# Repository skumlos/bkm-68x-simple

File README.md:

BKM-68X alternative input board

This project aims to serve as an alternative to the crazy expensive Sony BKM-68X RGB/YPbPr
input card for Sony BVM-A monitors like the BVM-A14F5, A20F1, A24E1W and A32E1W (M/U/A).

The board is rather simple albeit has some components that are not so simple to hand solder,
and it also has a quite high component count (due to a load of resistors and caps).

It's buildup is basically an analog section that deals with video, and a digital section
that speaks to the monitor.

The analog section buffers the video by an THS7374 (with the LPF disabled!) and throws
those through an ADG1611 (or compatible) switch, working via the VIDEO_OE_X signal from
the FPGA. The Y/G signal is first routed through an ISL4089 which strips the sync part 
(if needed) from the signal to avoid too bright picture in YPbPr and SoG signals. This
is however only done if the input is YPbPr at 480p and below and for RGsB signals.
In version 1.1 of the software, this can be switched by turning aperture on. This might
be removed later though, as this is somewhat for testing.

The sync signal is separated through an ISL59885 with a color filter in front (as per
the datasheet), and the signal to be separated (external or Y signal) is chosen via
INT_EXT_X signal to an FSA2257MUX switch.

These are then passed to the FPGA which detects sync polarity and changes accordingly
to positive sync, and then sends the two signals into the monitor.

The digital section consists of a FPGA (efinix Trion T8Q144) with a buttload of schmitt
triggers and line drivers, all replicated from the original 68X service manual. The
card thus tries to be electrically similar to the original, at the interface level.

The FPGA is expected to be programmed with the HDL from https://github.com/skumlos/bkm-68x-fpga

75 Ohm termination can be selected by the switches, which either terminates, or passthroughs
(in that case external terminators are needed, unless signal is actually passed through to a
terminating monitor).

The card has no aperture circuit so it can only pass the signal straight through to the monitor
as it originally is (buffered and level conditioned).

Compared to the original BKM-68X, this has severely better sync handling seemingly.

The list of tested consoles that syncs fine as of revision E1 is:

SNES (2CHIP US) 60Hz (CSYNC)

SNES (1CHIP FAT US) 60Hz (CSYNC)

SNES (2CHIP EU) 50Hz (Sync on luma)

SNES (1CHIP EU, SNSP-1CHIP-01) 50Hz (Sync on luma)

Genesis (US) 60Hz (CVBS sync)

Genesis 2 (US) 60Hz (CSYNC)

Mega Drive (EU) 50Hz (CVBS sync)

Mega Drive 2 (EU, DFO) 60Hz (CSYNC)

Mega Drive 2 (EU, DFO) 50Hz (CSYNC)

Master System (on Genesis through Power Base) 60Hz (CVBS sync)

Master System (EU, DFO) 60Hz (CSYNC)

Master System (EU, DFO) 50Hz (CSYNC)

Master System (EU, VA3, no DFO) 60Hz (59,38Hz) (CSYNC)

Master System (EU, VA3, no DFO) 50Hz (CSYNC)

Nintendo 64 (NUSJ) 60Hz (THS7314 RGB) (CSYNC)

Wii (EU) 576i 50Hz (YPbPr)

Wii (EU) 480i 60Hz (YPbPr)

Wii (EU) 480p 60Hz (YPbPr)

PSone SCPH-101 (EU) (MM3+MFO) 60Hz (RGC CSYNC)

PSone SCPH-101 (EU) (MM3+MFO) 50Hz (RGC CSYNC)

PS2 (US) 240p/480i 60Hz (RGBS)

PS2 (US) 480p 60Hz (RGsB)

PS2 (US) 240p/480i/480p (YPbPr)

PS3 (EU) 576i 50Hz (YPbPr)

PS3 (EU) 576p 50Hz (YPbPr)

PS3 (EU) 720p 60Hz (YPbPr)

PS3 (EU) 1080i 60Hz (YPbPr)

PC Engine (White), External RGB mod (THS7374, Genesis 2 plug), 60Hz (CSYNC)

Analogue Nt Mini 2.0 60Hz RGBS (so CSYNC)

Amiga 500 RGBS (PAL) 50Hz (CSYNC)

Xbox 360 (EU) 480i/480p/720p 50/60Hz (YPbPr)

Xbox 360 (EU) 1080i 60Hz (YPbPr) (1080i 50Hz seems to just flicker. Does the same with original 68X)

A load of MiSTer cores which are normally deemed problematic, including DoDonPachi
whose whack VSYNC of 57.6 Hz makes the original BKM-68X scroll the picture with a
steady OSD, while this version has a steady picture with a rolling OSD :)

Master System with CVBS sync works, but sometimes "glitches". This is apparently
due to the quite noisy CVBS signal, which the sync separator picks up. Without
the color filter it is unusable.

It is generally recommended to use CSYNC signals at 75 Ohm levels.

Revision history:

F1-5: A ton of changes, most notably Intel MAX10 FPGA has been change to efinix Trion T8Q144 and ADG734 -> FSA2257MUX

E1: Add "proper" 5V->3.3V translation for sync lines

E: Add "Y/G normalization" control from FPGA

D1: Add STBY_5V pinheader for easier outside-monitor-programming of FPGA.

D: Add DC restore and sync-removal circuit on Y/G line

C1: Minor layout changes

C: Added mounting screw brackets and shortened board for a PCB front, change switch to LFCSP version

B: Added onboard FPGA, color filter, rerouted signals.

A: Initial version

More information @ https://www.immerhax.com

Credits:
Mathias Hyldgaard for providing me with a BVM-A20, which initiated the whole project!
Bob from RetroRGB for testing and listening to my woes :)
The secret benefactor(s) of the original BKM-68X which made the whole project much easier, and ultimately made it possible!
Steve Nutter for being a helpful guy within the pro monitor scene!
The people on the CRT discord and Professional and Broadcast Monitor Facebook group!

(2021) Martin Hejnfelt, martin@hejnfelt.com

This work is released under the CERN Open Hardware Licence version 2 (CERN-OHL-W), see LICENCE.TXT

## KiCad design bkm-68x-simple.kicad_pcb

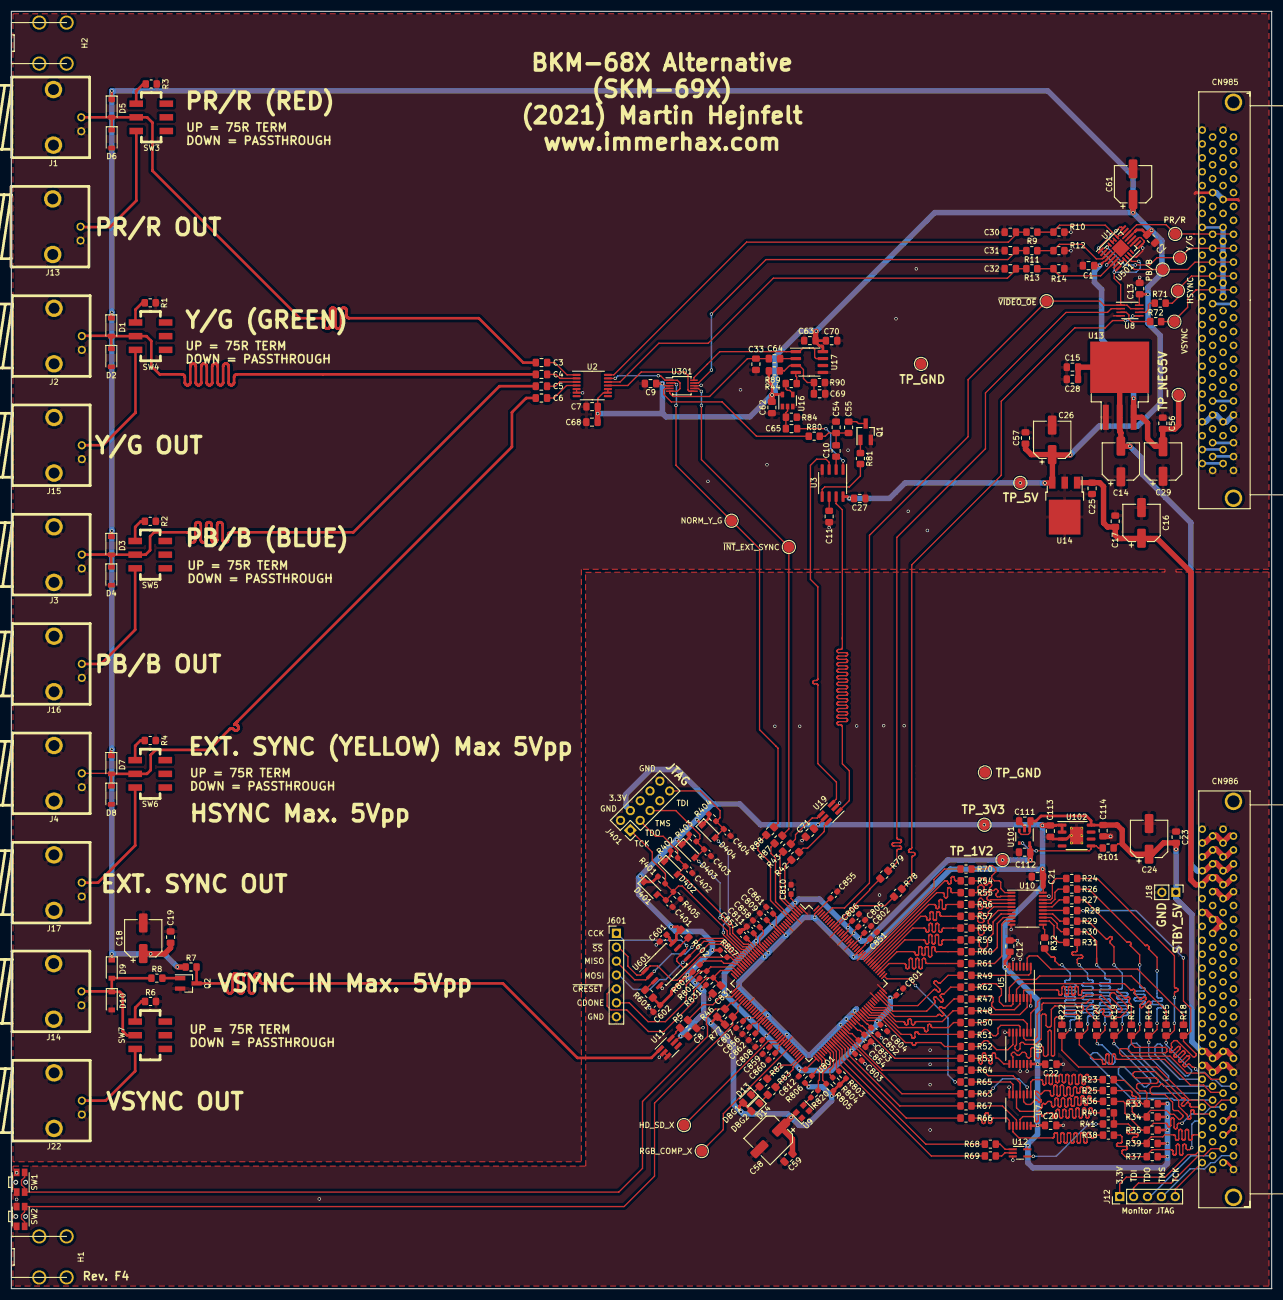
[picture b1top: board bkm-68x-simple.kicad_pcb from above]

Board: 2 copper layers, 230.4 x 233.5 mm, 264 parts (0 on the bottom side), 197 nets.

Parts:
C1, C2, C3, C4, C5, C6, C7, C8, C9, C10, C12, C13, C15, C17, C19, C20, C21, C22, C27, C56, C57, C59, C62, C63, C64, C71: 0.1uF; C_0805_2012Metric_Pad1.18x1.45mm_HandSolder
C11: 56nF; C_0805_2012Metric_Pad1.18x1.45mm_HandSolder
C14, C16, C18, C61: 100uF; CP_Elec_6.3x5.3
C23, C111, C112, C113, C114: 1uF; C_0805_2012Metric_Pad1.18x1.45mm_HandSolder
C24, C58: 100uF; CP_Elec_6.3x5.4
C25, C28, C68, C70, C831: 10uF; C_0805_2012Metric_Pad1.18x1.45mm_HandSolder
C26: 330uF/LOW_ESR; CP_Elec_6.3x7.7
C29: 330uF/LOW_ESR; CP_Elec_6.3x5.8
C30, C31, C32, C69: NM; C_0805_2012Metric_Pad1.18x1.45mm_HandSolder
C33: 22pF; C_0805_2012Metric_Pad1.18x1.45mm_HandSolder
C54: 100pF; C_0805_2012Metric_Pad1.18x1.45mm_HandSolder
C55: 470pF; C_0805_2012Metric_Pad1.18x1.45mm_HandSolder
C65: 220pF; C_0805_2012Metric_Pad1.18x1.45mm_HandSolder
C401, C402, C403, C404: 10pF; C_0603_1608Metric_Pad1.08x0.95mm_HandSolder
C601, C602, C801, C802, C803, C804, C805, C806, C807, C808, C809, C810, C811, C812, C851, C852, C853, C854, C855, C856, C857, C858, C859, C860, C861, C862: 0.1uF; C_0603_1608Metric_Pad1.08x0.95mm_HandSolder
CN985, CN986: mezz-conn-02x50; TX24-100R-LT-H1E
D1, D2, D3, D4, D5, D6, D7, D8, D9, D10, D401, D402, D403, D404: NM; D_SOD-123
D13: DEBUG1; LED_0805_2012Metric_Pad1.15x1.40mm_HandSolder
D14: DEBUG2; LED_0805_2012Metric_Pad1.15x1.40mm_HandSolder
H1, H2: Keystone 7794; 7794-X
J1: PR_R; BNC-THT
J2: Y_G; BNC-THT
J3: PB_B; BNC-THT
J4: EXT_SYNC; BNC-THT
J5: TP_Y_G; TestPoint_Pad_D2.0mm
J6: TP_PB_B; TestPoint_Pad_D2.0mm
J7: TP_PR_R; TestPoint_Pad_D2.0mm
J8: TP_HSYNC; TestPoint_Pad_D2.0mm
J9: TP_INT_EXT_SYNC; TestPoint_Pad_D2.0mm
J10: TP_VIDEO_OE; TestPoint_Pad_D2.0mm
J11: TP_VSYNC; TestPoint_Pad_D2.0mm
J12: JTAG; PinHeader_1x05_P2.54mm_Vertical
J13: PR_R_OUT; BNC-THT
J14: VSYNC_DISCRETE; BNC-THT
J15: Y_G_OUT; BNC-THT
J16: PB_B_OUT; BNC-THT
J17: EXT_SYNC_OUT; BNC-THT
J18: Conn_01x02_Male; PinHeader_1x02_P2.54mm_Vertical
J19: TP_NORM_Y_G; TestPoint_Pad_D2.0mm
J20: TP_RGB_COMP_X; TestPoint_Pad_D2.0mm
J21: TP_HD_SD_X; TestPoint_Pad_D2.0mm
J22: VSYNC_DISCRETE_OUT; BNC-THT
J101: TP_1V2; TestPoint_Pad_D2.0mm
J102: TP_3V3; TestPoint_Pad_D2.0mm
J103: TP_GNDD1; TestPoint_Pad_D2.0mm
J201: TP_NEG5V; TestPoint_Pad_D2.0mm
J202: TP_5V; TestPoint_Pad_D2.0mm
J203: TP_GNDA1; TestPoint_Pad_D2.0mm
J401: JTAG; PinHeader_2x05_P2.54mm_Vertical
J601: SPI_PROG; PinHeader_1x07_P2.54mm_Vertical
Q1, Q2: MMBT3904; SOT-23_Handsoldering
R1, R2, R3, R4, R6, R10, R12, R14: 75R; R_0805_2012Metric_Pad1.20x1.40mm_HandSolder
R5, R15, R16, R17, R18, R19, R20, R21, R22, R23, R25, R36, R38, R42, R43, R47, R48, R49, R50, R51, R52, R53, R62, R63, R64, R65, R66, R67: 68R; R_0805_2012Metric_Pad1.20x1.40mm_HandSolder
R7, R44: 1K; R_0805_2012Metric_Pad1.20x1.40mm_HandSolder
R8, R46, R77, R81, R84, R101, R601, R602: 10K; R_0805_2012Metric_Pad1.20x1.40mm_HandSolder
R9, R11, R13: 150R; R_0805_2012Metric_Pad1.20x1.40mm_HandSolder
R24, R26, R27, R28, R29, R30, R31, R32, R71, R72: 47R; R_0805_2012Metric_Pad1.20x1.40mm_HandSolder
R33, R34, R35, R39: 47K; R_0805_2012Metric_Pad1.20x1.40mm_HandSolder
R37: 22K; R_0805_2012Metric_Pad1.20x1.40mm_HandSolder
R40, R41, R54, R55, R56, R57, R58, R59, R60, R61, R68, R69, R70, R78, R79, R87, R88: 22R; R_0805_2012Metric_Pad1.20x1.40mm_HandSolder
R80: 100R; R_0805_2012Metric_Pad1.20x1.40mm_HandSolder
R82: 470R; R_0805_2012Metric_Pad1.20x1.40mm_HandSolder
R83: 390R; R_0805_2012Metric_Pad1.20x1.40mm_HandSolder
R89: NM; R_0805_2012Metric_Pad1.20x1.40mm_HandSolder
R90: 0R; R_0805_2012Metric_Pad1.20x1.40mm_HandSolder
R401, R402, R403, R404, R801, R802, R803, R804, R805, R806, R807, R831: 10K; R_0603_1608Metric_Pad0.98x0.95mm_HandSolder
R405: 1K; R_0603_1608Metric_Pad0.98x0.95mm_HandSolder
R820: 22R; R_0603_1608Metric_Pad0.98x0.95mm_HandSolder
SW1, SW2: FORCE_VIDEO; SW_SPST_EVQP7C
SW3: PR_R_TERM; JS202011SCQN
SW4: Y_G_TERM; JS202011SCQN
SW5: PB_B_TERM; JS202011SCQN
SW6, SW7: EXT_SYNC_TERM; JS202011SCQN
U1: ADG1611BCPZ; LFCSP-16-1EP_4x4mm_P0.65mm_EP2.4x2.4mm
U2: THS7374; TSSOP-14_4.4x5mm_P0.65mm
U3: ISL59885; SOIC-8_3.9x4.9mm_P1.27mm
U5, U6, U7: 74LVC14A; TSSOP-14_4.4x5mm_P0.65mm
U8: TC7WH125; SSOP-8_2.95x2.8mm_P0.65mm
U9: KC2520Z50; Oscillator_SMD_Kyocera_KC2520Z-4Pin_2.5x2.0mm
U10: 74LVC541A; TSSOP-20_4.4x6.5mm_P0.65mm
U11, U19: 74LVC2G34; SOT-23-6_Handsoldering
U12: TC7SZ125FU; SOT-353_SC-70-5_Handsoldering
U13: LM2990SX-5.0; TO-263-3_TabPin2
U14: BA50BC0FP-E2; TO-252-3_TabPin2
U16: SN74LVC1G14DBV; SOT-23-5
U17: ISL4089; SOIC-8_3.9x4.9mm_P1.27mm
U101: NCV8164ASN120T1G; TSOP-5_1.65x3.05mm_P0.95mm
U102: BD33HC0WEFJ-E2; HTSOP-8-1EP_3.9x4.9mm_P1.27mm_EP2.4x3.2mm_ThermalVias
U301: FSA2257MUX; MSOP-10_3x3mm_P0.5mm
U501: ADG1611; TSSOP-16_4.4x5mm_P0.65mm
U601: W25Q128JVS; SOIC-8_5.23x5.23mm_P1.27mm
U801: T8Q144; TQFP-144_20x20mm_P0.5mm

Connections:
100PCT_P: CN985.A47, CN985.B47
+1V2: C112.1, C801.1, C802.1, C803.1, C804.1, C805.1, C806.1, C807.1, C808.1, C809.1, C810.1, C811.1, C812.1, J101.1, U101.5, U801.2, U801.13, U801.22, U801.49, U801.57, U801.73, U801.85, U801.96, U801.107, U801.125, U801.128, U801.130
+3V3: C8.2, C12.1, C20.1, C21.1, C22.2, C58.1, C59.1, C71.2, C113.1, C601.2, C602.1, C851.1, C852.1, C853.1, C854.1, C855.1, C856.1, C857.1, C858.1, C859.1, C860.1, C861.1, C862.1, D13.2, D14.2, D401.1, D402.1, D403.1, D404.1, J102.1, J401.4, R33.1, R34.1, R35.1, R37.1, R39.1, R46.2, R77.2, R401.2, R402.2, R403.2, R404.2, R601.2, R602.2, R801.1, R802.1, R803.1, R804.1, R805.1, R806.1, R807.2, R831.2, U5.14, U6.14, U7.14, U9.4, U10.20, U11.5, U12.5, U19.5, U102.1, U102.2, U601.8, U801.12, U801.21, U801.23, U801.51, U801.52, U801.62, U801.63, U801.88, U801.91, U801.95, U801.122, U801.143
+5VA: C2.1, C7.2, C9.1, C13.1, C18.1, C19.1, C26.1, C27.1, C57.1, C61.1, C62.2, C63.1, C68.1, C70.1, D1.1, D3.1, D5.1, D7.1, D9.1, J202.1, R7.1, R89.1, U1.11, U2.9, U2.10, U3.8, U8.8, U14.3, U16.5, U17.8, U301.3, U501.13
+6V: C16.1, C17.1, C25.1, CN986.A8, CN986.A9, CN986.B8, CN986.B9, U14.1
+15V: CN986.A4, CN986.A5, CN986.B4, CN986.B5
-5VA: C1.1, C29.2, C56.1, J201.1, U1.2, U1.17, U13.3, U501.4
-6V: C14.2, C15.1, C28.1, CN986.A6, CN986.A7, CN986.B6, CN986.B7, U13.2
-15V: CN986.A2, CN986.A3, CN986.B2, CN986.B3
/FPGA/CLK_50MHz: R820.1, U9.3
/FPGA/DBG1: R82.2, U801.71
/FPGA/DBG2: R83.2, U801.72
/FPGA/FPGA_ADIN0: R62.2, U801.105
/FPGA/FPGA_ADIN1: R47.2, U801.101
/FPGA/FPGA_ADIN2: R48.2, U801.100
/FPGA/FPGA_ADIN3: R49.2, U801.106
/FPGA/FPGA_ADIN4: R50.2, U801.99
/FPGA/FPGA_ADIN5: R51.2, U801.98
/FPGA/FPGA_ADIN6: R52.2, U801.97
/FPGA/FPGA_ADIN7: R53.2, U801.93
/FPGA/FPGA_ADOUT0: R54.2, U801.118
/FPGA/FPGA_ADOUT1: R55.2, U801.117
/FPGA/FPGA_ADOUT2: R56.2, U801.116
/FPGA/FPGA_ADOUT3: R57.2, U801.115
/FPGA/FPGA_ADOUT4: R58.2, U801.114
/FPGA/FPGA_ADOUT5: R59.2, U801.113
/FPGA/FPGA_ADOUT6: R60.2, U801.112
/FPGA/FPGA_ADOUT7: R61.2, U801.111
/FPGA/FPGA_CLK_RW: R66.1, U801.83
/FPGA/FPGA_R_~W: R63.1, U801.86
/FPGA/FPGA_~A~_D: R64.1, U801.87
/FPGA/TCK: C401.1, D401.2, J401.1, R401.1, R405.2, U801.26
/FPGA/TDI: C404.1, D404.2, J401.9, R404.1, U801.27
/FPGA/TDO: C402.1, D402.2, J401.3, R402.1, U801.24
/FPGA/TMS: C403.1, D403.2, J401.5, R403.1, U801.25
/FPGA/~FPGA_AD_OE: R70.2, U801.119
/FPGA/~FPGA_IRQ: R69.1, U801.81
/FPGA/~FPGA_IRQ_OE: R68.1, U801.82
/FPGA/~FPGA_RESET: R65.1, U801.109
/FPGA/~FPGA_SLOT: R67.1, U801.84
/Video/CSYNC: C65.1, U3.1
/Video/ISL_SD_HD: R81.2, U3.5
/Video/PB_B_L: R13.2, R14.2, U1.4, U501.6
/Video/PR_R_L: R9.2, R10.2, U1.13, U501.15
/Video/Y_G_L: R11.2, R12.2, U1.1, U501.3
/Video/~CSYNC: R44.1, U17.4
AD0: CN986.A37, R15.1, R24.1
AD1: CN986.A38, R16.1, R26.1
AD2: CN986.B37, R17.1, R27.1
AD3: CN986.B38, R18.1, R28.1
AD4: CN986.A39, R19.1, R29.1
AD5: CN986.A40, R20.1, R30.1
AD6: CN986.B39, R21.1, R31.1
AD7: CN986.B40, R22.1, R32.1
CDONE: J601.6, R801.2, U801.34
CLK_RW: CN986.A43, R37.2, R38.2
EXT_SYNC_AMP: U2.11, U301.6
EXT_SYNC_IN: C6.2, D7.2, D8.1, J4.1, SW6.2
FORCE_VIDEO: R46.1, SW1.1, U801.40
FORCE_VIDEO2: R77.1, SW2.1, U801.42
GND: C1.2, C2.2, C7.1, C8.1, C9.2, C11.1, C12.2, C13.2, C14.1, C15.2, C16.2, C17.2, C18.2, C19.2, C20.2, C21.2, C22.1, C23.2, C24.2, C25.2, C26.2, C27.2, C28.2, C29.1, C30.2, C31.2, C32.2, C33.1, C54.1, C56.2, C57.2, C58.2, C59.2, C61.2, C62.1, C63.2, C68.2, C69.1, C70.2, C71.1, C111.2, C112.2, C113.2, C114.2, C401.2, C402.2, C403.2, C404.2, C601.1, C602.2, C801.2, C802.2, C803.2, C804.2, C805.2, C806.2, C807.2, C808.2, C809.2, C810.2, C811.2, C812.2, C831.2, C851.2, C852.2, C853.2, C854.2, C855.2, C856.2, C857.2, C858.2, C859.2, C860.2, C861.2, C862.2, CN985.A1, CN985.A10, CN985.A15, CN985.A17, CN985.A19, CN985.A21, CN985.A23, CN985.A25, CN985.A42, CN985.A43, CN985.A46, CN985.A48, CN985.A50, CN985.B1, CN985.B11, CN985.B15, CN985.B17, CN985.B19, CN985.B21, CN985.B23, CN985.B25, CN985.B42, CN985.B43, CN985.B46, CN985.B48, CN985.B50, CN986.A1, CN986.A10, CN986.A11, CN986.A13, CN986.A14, CN986.A15, CN986.A16, CN986.A35, CN986.A36, CN986.A50, CN986.B1, CN986.B10, CN986.B11, CN986.B15, CN986.B35, CN986.B36, CN986.B42, CN986.B43, CN986.B44, CN986.B45, CN986.B46, CN986.B49, CN986.B50, D2.2, D4.2, D6.2, D8.2, D10.2, J1.2, J2.2, J3.2, J4.2, J13.2, J14.2, J15.2, J16.2, J17.2, J18.2, J22.2, J103.1, J203.1, J401.2, J401.10, J601.7, Q1.2, Q2.2, R1.2, R2.2, R3.2, R4.2, R6.2, R10.1, R12.1, R14.1, R84.2, R90.2, R405.1, SW1.2, SW2.2, U1.3, U1.7, U1.9, U2.5, U2.6, U3.4, U5.7, U5.11, U5.13, U6.7, U6.11, U6.13, U7.7, U8.4, U9.2, U10.10, U10.19, U11.2, U11.3, U12.3, U13.1, U14.2, U16.3, U17.5, U19.2, U101.2, U102.3, U102.9, U301.8, U501.5, U501.9, U501.11, U601.4, U801.1, U801.5, U801.9, U801.37, U801.44, U801.50, U801.64, U801.94, U801.104, U801.108, U801.120, U801.121, U801.126, U801.127, U801.129, U801.133
HD_SD_X: J21.1, U801.61
HSYNC: CN985.A22, CN985.B22, J8.1, R71.2
HSYNC_OUT: R79.2, U8.2
HSYNC_SEP: U3.7, U19.1
HSYNC_SEP_BUF: R42.1, U801.3
INT_~EXT~_SYNC: J9.1, R87.2, U301.7
JTAG_3.3V: CN986.A47, J12.1
JTAG_TCK: CN986.A49, J12.5
JTAG_TDI: CN986.B47, J12.2
JTAG_TDO: CN986.A48, J12.3
JTAG_TMS: CN986.B48, J12.4
NORM_Y_G: J19.1, R88.2, U301.2
unnamed: C3.1, U2.1
unnamed: C4.1, U2.2
unnamed: C5.1, U2.3
unnamed: C6.1, U2.4
unnamed: C10.1, U3.2
unnamed: C11.2, U3.6
unnamed: C55.1, Q1.3
unnamed: C64.2, U17.2
unnamed: C65.2, R84.1, U16.2
unnamed: C69.2, R89.2, R90.1, U17.3
unnamed: D9.2, D10.1, J14.1, R8.1, SW7.2
unnamed: D13.1, R82.1
unnamed: D14.1, R83.1
unnamed: J13.1, SW3.3
unnamed: J15.1, SW4.3
unnamed: J16.1, SW5.3
unnamed: J17.1, SW6.3
unnamed: J22.1, SW7.3
unnamed: Q1.1, R81.1
unnamed: Q2.1, R8.2
unnamed: R1.1, SW4.1
unnamed: R2.1, SW5.1
unnamed: R3.1, SW3.1
unnamed: R4.1, SW6.1
unnamed: R5.2, U11.6
unnamed: R6.1, SW7.1
unnamed: R15.2, U5.1
unnamed: R16.2, U5.3
unnamed: R17.2, U5.5
unnamed: R18.2, U5.9
unnamed: R19.2, U6.1
unnamed: R20.2, U6.3
unnamed: R21.2, U6.5
unnamed: R22.2, U6.9
unnamed: R23.1, U7.1
unnamed: R24.2, U10.18
unnamed: R25.1, U7.3
unnamed: R26.2, U10.17
unnamed: R27.2, U10.16
unnamed: R28.2, U10.15
unnamed: R29.2, U10.14
unnamed: R30.2, U10.13
unnamed: R31.2, U10.12
unnamed: R32.2, U10.11
unnamed: R36.1, U7.5
unnamed: R38.1, U7.9
unnamed: R40.1, U7.11
unnamed: R41.1, U12.4
unnamed: R42.2, U19.6
unnamed: R43.2, U19.4
unnamed: R44.2, U16.4
unnamed: R47.1, U5.4
unnamed: R48.1, U5.6
unnamed: R49.1, U5.8
unnamed: R50.1, U6.2
unnamed: R51.1, U6.4
unnamed: R52.1, U6.6
unnamed: R53.1, U6.8
unnamed: R54.1, U10.2
unnamed: R55.1, U10.3
unnamed: R56.1, U10.4
unnamed: R57.1, U10.5
unnamed: R58.1, U10.6
unnamed: R59.1, U10.7
unnamed: R60.1, U10.8
unnamed: R61.1, U10.9
unnamed: R62.1, U5.2
unnamed: R63.2, U7.2
unnamed: R64.2, U7.4
unnamed: R65.2, U7.6
unnamed: R66.2, U7.8
unnamed: R67.2, U7.10
unnamed: R68.2, U12.1
unnamed: R69.2, U12.2
unnamed: R70.1, U10.1
unnamed: R71.1, U8.6
unnamed: R72.1, U8.3
unnamed: R78.1, U801.134
unnamed: R79.1, U801.135
unnamed: R87.1, U801.6
unnamed: R88.1, U801.7
unnamed: R601.1, U601.3
unnamed: R602.1, U601.7
unnamed: R802.2, U801.32
unnamed: R803.2, U801.80
unnamed: R804.2, U801.79
unnamed: R805.2, U801.78
unnamed: R806.2, U801.74
unnamed: R820.2, U801.75
PB_B: CN985.A20, CN985.B20, J6.1, U1.5, U501.7
PB_B_AMP: C32.1, R13.1, U2.12
PB_B_IN: C5.2, D3.2, D4.1, J3.1, SW5.2
PR_R: CN985.A16, CN985.B16, J7.1, U1.12, U501.14
PR_R_AMP: C30.1, R9.1, U2.14
PR_R_IN: C3.2, D5.2, D6.1, J1.1, SW3.2
RGB_COMP_X: J20.1, U801.66
R_~W: CN986.A41, R23.2, R33.2
SETUP_P: CN985.A49, CN985.B49
STBY_5V: C23.1, C24.1, C111.1, C114.1, CN986.A33, CN986.A34, CN986.B33, CN986.B34, J18.1, R101.1, U101.1, U101.3, U102.8
SYNC_SRC: R80.1, U301.4
SYNC_SRC_FILTER: C10.2, C54.2, C55.2, R80.2
VCORE_GOOD: R101.2, U101.4, U102.5
VIDEO: CN985.A26, CN985.B26
VIDEO_COMP: CN985.A40, CN985.B40
VSYNC: CN985.A24, CN985.B24, J11.1, R72.2
VSYNC_DISCRETE_BUF: R5.1, U801.38
VSYNC_DISCRETE_IN: Q2.3, R7.2, U11.1
VSYNC_OUT: R78.2, U8.5
VSYNC_SEP: U3.3, U19.3
VSYNC_SEP_BUF: R43.1, U801.4
Y_G: CN985.A18, CN985.B18, J5.1, U1.16, U501.2
Y_G_AMP: C33.2, C64.1, U2.13, U301.1, U301.5
Y_G_IN: C4.2, D1.2, D2.1, J2.1, SW4.2
Y_G_NORM: U17.1, U17.7, U301.10
Y_G_SW: C31.1, R11.1, U301.9
~A~_D: CN986.A42, R25.2, R34.2
~CRESET: C831.1, J601.5, R831.1, U801.35
~FPGA_CCK: J601.1, U601.6, U801.30
~FPGA_MISO: J601.3, U601.2, U801.28
~FPGA_MOSI: J601.4, U601.5, U801.29
~FPGA_SS: J601.2, R807.1, U601.1, U801.31
~RESET: CN986.B41, R35.2, R36.2
~SLOT~_~IRQ~: CN986.A45, R39.2, R40.2, R41.2
~VIDEO_OE: J10.1, U1.6, U1.14, U1.15, U8.1, U8.7, U501.1, U501.8, U501.16, U801.140

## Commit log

2021-03-21 Minor fixes and cleanups
2021-04-18 A lotta fixes
2021-05-14 Onboard FPGA, passthroughs and a lot of other stuff
2021-05-14 Added README
2021-05-14 Fixed formatting in README
2021-05-16 Updated some component values
2021-05-16 Fixes and additions
2021-05-17 Shortened board slightly for PCB front, rev C
2021-05-25 Replace ADG1611BRUZ with BCPZ
    Should also be compatible with Vishay DG1411EEN-T1-GE4
2021-06-01 Rev C1
2021-06-01 Add Rev C1 plot
2021-06-01 Added credits to README
2021-07-01 Name screw mount part, add licence
2021-07-15 Revision D
2021-07-17 Revision D1
2021-08-19 Rev. E
2021-08-19 Rev. E1
2021-08-19 Missing libs
2021-08-30 Updated plots
2022-04-12 Rev. F1
2022-04-13 Added vsync out
2022-05-02 Rev. F2
2022-06-15 Rev. F4
2022-09-28 Minor updates
